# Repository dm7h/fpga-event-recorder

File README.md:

FPGA-Event-Recorder
-------------------

This project implements a FPGA based event recorder using the open source toolchain IceStorm. 
Similar to a logic analyzer it records logic level input signals, but in contrast to a logic analyzer it does not provide a continuous stream of the signal state. Instead the signals are filtered at capture time to match only relevant input combinations and signal changes. Using predefined events to filter the input stream is especially suitable for the analysis of known signals that are to be captured and examined at high temporal resolution.
The implementation of the event recorder is done on a Raspberry Pi Zero with a Lattice iCE40-based FPGA shield and is realized using the IcoSoc project with the IceStorm toolchain.   

### Getting started:

* install the IceStorm toolchain
see http://www.clifford.at/icestorm/#install

* install the RISC-V toolchain
```bash
git clone git@github.com:cliffordwolf/picorv32.git
cd picorv32
make download-tools
make -j$(nproc) build-tools                                                               
```
(can take a while)

* download the IcoSoc port for IceZero (on your local machine)
```bash
cd ..
git clone https://github.com/dm7h/icozsoc.git
```
* configure SSH on the raspi
```bash
# see: https://www.raspberrypi.org/documentation/remote-access/ssh/passwordless.md
# export ssh host, eg. pi@zero oder pi@192.168.1.43:
export SSH_RASPI=pi@zero
# check password-less ssh connection
ssh $SSH_RASPI                                                                               $
```
* install `icozctl` on the raspi 
```bash
git clone https://github.com/dm7h/icozctl
cd icozctl
sudo make install
```
* compile and flash the bitstream (local machine)
```bash
cd ../icosoc/examples/event-recorder/
make prog_flash
```
* on the raspi, edit `ìcozctl/config.yml` to your liking
```yaml
# event configuration
events: 
  - start:
          trigger: u
          funcion: start

  - stop:
          trigger: d
          function: stop

  - clk_up:
          trigger: 1u

  - clk_down:
          trigger: 1d
```
* start recording events `
```bash
icozctl -s -c config.yml -o midi_clock.vcd
```
see `icozctl -h` for options

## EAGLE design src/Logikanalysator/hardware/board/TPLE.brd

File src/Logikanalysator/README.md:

Logikanalysator
---------------

Hubert Högl, <Hubert.Hoegl@hs-augsburg.de>, 2017-12-04 

Das Logikanalysator-Projekt "USB-TPLE" entstand in der Bachelorarbeit
von Andreas Müller in 2010. Die Dateien aus der Bachelorarbeit sind im
Ordner 

```
USB-TPLE
```

Später wurde das Projekt in einer Projektarbeit im WS13/14 noch einmal
stark überarbeitet. Meine Aufgabenstellung ist auf dieser Wiki-Seite:

http://hhoegl.informatik.hs-augsburg.de/hhwiki/Logikanalysator

Die Ergebnisse sind in den Verzeichnissen:

```
cpld-firmware
Doku
Firmware-Mikrocontroller
hardware
jtag-LufaVirtualSerial
jtag-staplplayer
pc-software
signalgenerator-de1
sigrok-integration
```

In `Doku/Wiki/index.html` ist ein Grossteil der Doku aus dem Trac Wiki
übernommen:

  https://io.informatik.fh-augsburg.de/cgi-bin/trac_Logikanalysator.cgi/wiki/

Den damaligen "Trac" Projektserver gibt es immer noch:

* TRAC: https://io.informatik.fh-augsburg.de/trac/Logikanalysator
* SVN: https://io.informatik.fh-augsburg.de/svn/Logikanalysator
* DAV: https://io.informatik.fh-augsburg.de/dav/Logikanalysator (Software)
* WWW: https://io.informatik.fh-augsburg.de/projekte/Logikanalysator

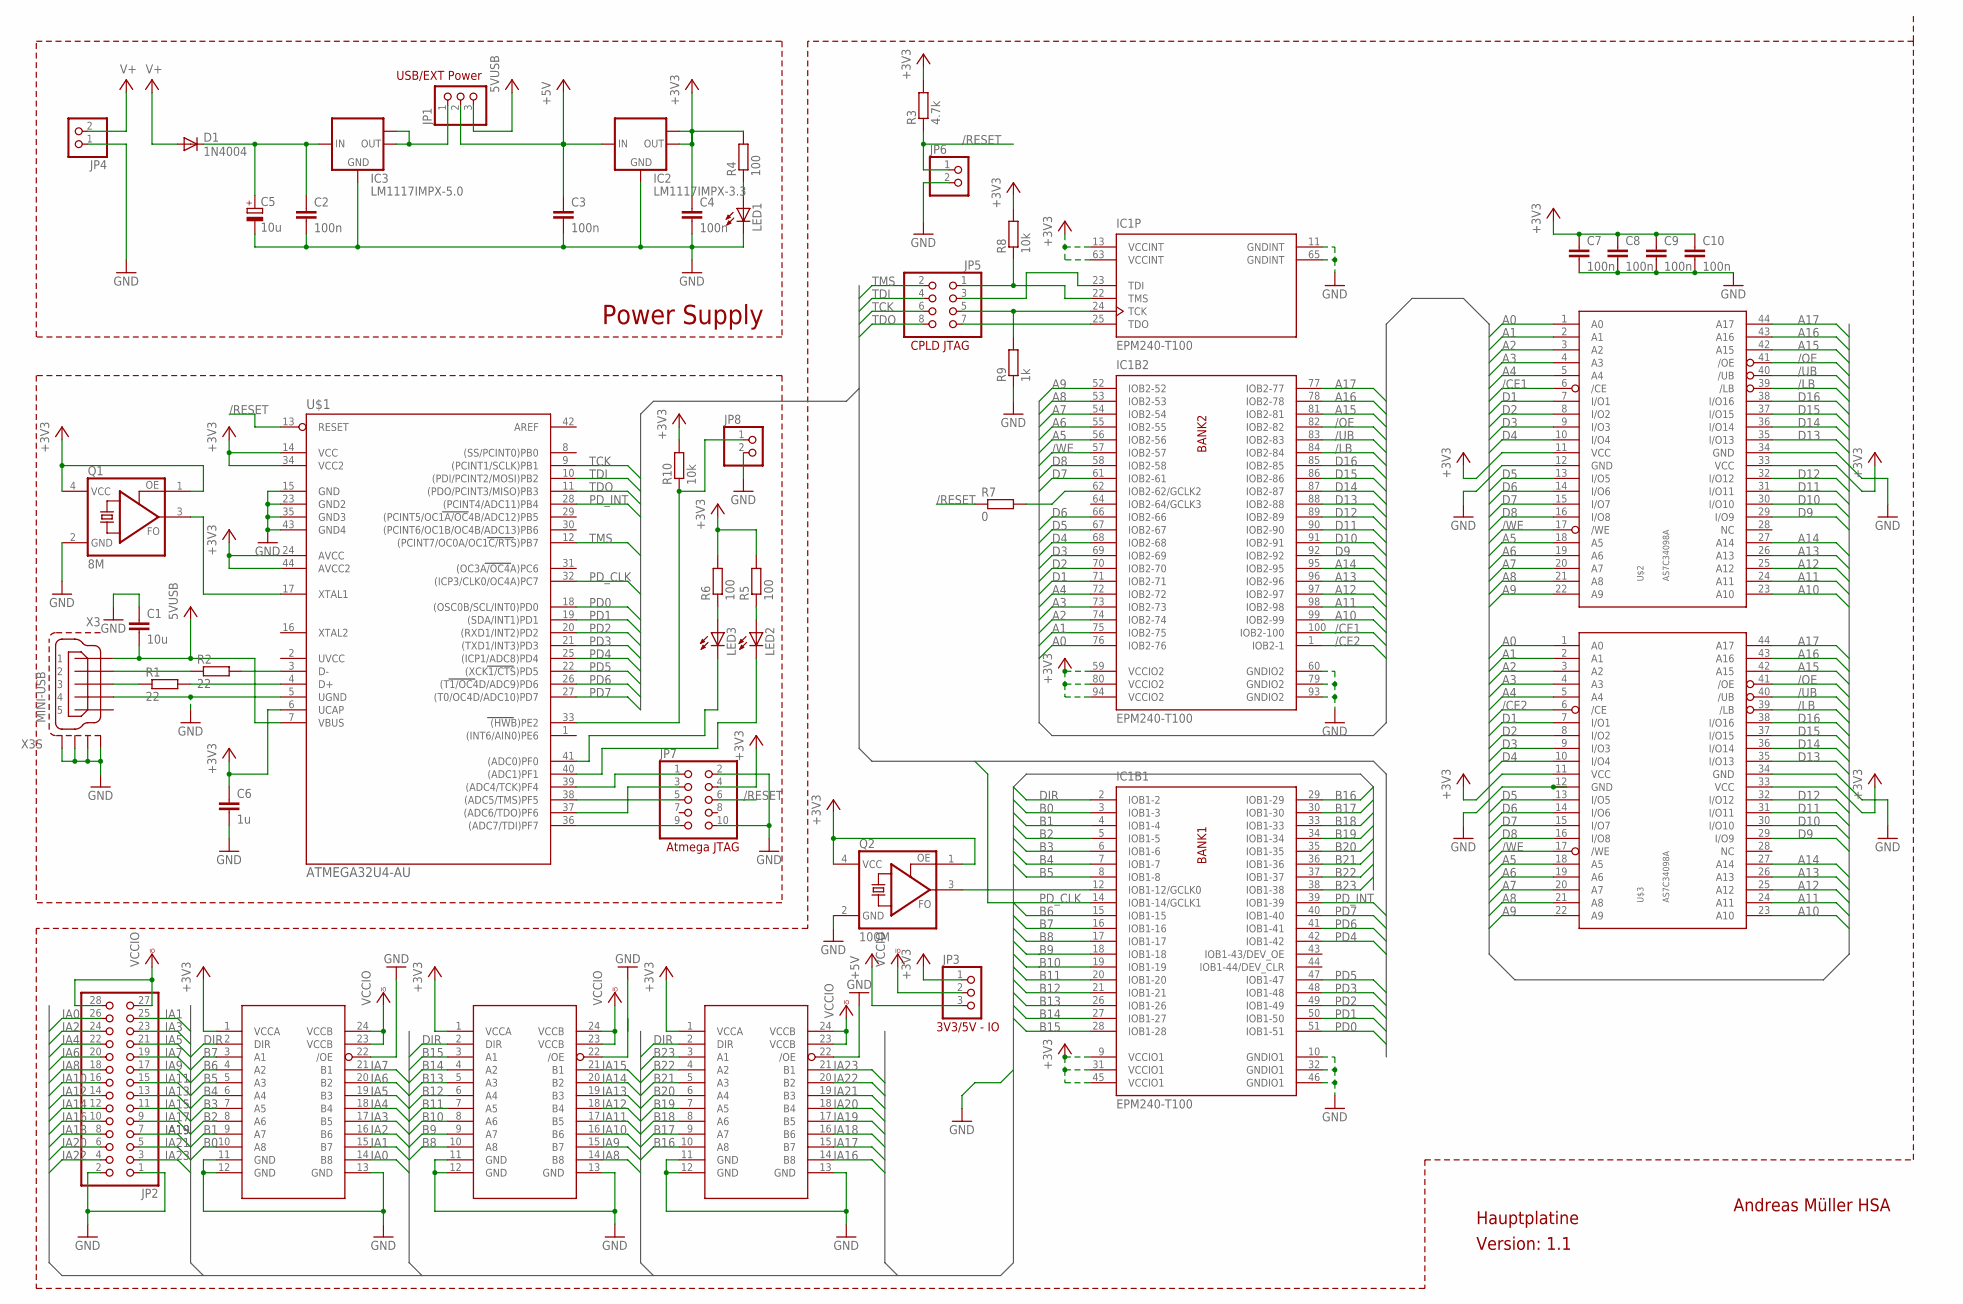
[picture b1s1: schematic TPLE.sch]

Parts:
C1: 10u; C3216
C2, C3, C4: 100n; C1206
C5: 10u; E2-5
C6: 1u; C0402
C7, C8, C9, C10: 100n; C0402
D1: 1N4004; DO41-10
IC1: EPM240-T100; TQFP100
IC2: LM1117IMPX-3.3; SOT223
IC3: LM1117IMPX-5.0; SOT223
JP1, JP3: PINHD-1X3; 1X03
JP2: PINHD-2X14; 2X14
JP4, JP6, JP8: PINHD-1X2; 1X02
JP5: PINHD-2X4; 2X04
JP7: PINHD-2X5; 2X05
LED1, LED2, LED3: LEDSMT1206; 1206
Q1: 8M; ASF
Q2: 100M; ASF
R1, R2: 22; M3216
R3: 4.7k; M3216
R4, R5, R6: 100; M3216
R7: 0; R0201
R8: 10k; M3216
R9: 1k; M3216
R10: 10k; R0402
U$1: ATMEGA32U4-AU; TQFP44
U$2, U$3: AS7C34098A; TSOP44-T2
U$4, U$5, U$6: SN74LVC8T245; TVSOP24
X3: MINI-USB; UX60A-MB-5ST

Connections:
+3V3: C4.1, C6.1, C7.1, C8.1, C9.1, C10.1, IC1.9 (VCCIO1), IC1.13 (VCCINT), IC1.31 (VCCIO1), IC1.45 (VCCIO1), IC1.59 (VCCIO2), IC1.63 (VCCINT), IC1.80 (VCCIO2), IC1.94 (VCCIO2), IC2.2 (OUT), IC2.TAB (OUT1), JP3.1, JP7.4, Q1.1 (OE), Q1.4 (VCC), Q2.1 (OE), Q2.4 (VCC), R3.2, R4.2, R5.2, R6.2, R8.2, R10.2, U$1.6 (UCAP), U$1.14 (VCC), U$1.24 (AVCC), U$1.34 (VCC2), U$1.44 (AVCC2), U$2.11 (VCC), U$2.33 (VCC), U$3.11 (VCC), U$3.33 (VCC), U$4.1 (VCCA), U$5.1 (VCCA), U$6.1 (VCCA)
+5V: C3.1, IC2.3 (IN), JP1.2, JP3.3
/CE1: IC1.100 (IOB2-100), U$2.6 (/CE)
/CE2: IC1.1 (IOB2-1), U$3.6 (/CE)
/LB: IC1.84 (IOB2-84), U$2.39 (/LB), U$3.39 (/LB)
/OE: IC1.82 (IOB2-82), U$2.41 (/OE), U$3.41 (/OE)
/RESET: JP6.1, JP7.6, R3.1, R7.1, U$1.13 (RESET)
/UB: IC1.83 (IOB2-83), U$2.40 (/UB), U$3.40 (/UB)
/WE: IC1.57 (IOB2-57), U$2.17 (/WE), U$3.17 (/WE)
A0: IC1.76 (IOB2-76), U$2.1 (A0), U$3.1 (A0)
A1: IC1.75 (IOB2-75), U$2.2 (A1), U$3.2 (A1)
A2: IC1.74 (IOB2-74), U$2.3 (A2), U$3.3 (A2)
A3: IC1.73 (IOB2-73), U$2.4 (A3), U$3.4 (A3)
A4: IC1.72 (IOB2-72), U$2.5 (A4), U$3.5 (A4)
A5: IC1.56 (IOB2-56), U$2.18 (A5), U$3.18 (A5)
A6: IC1.55 (IOB2-55), U$2.19 (A6), U$3.19 (A6)
A7: IC1.54 (IOB2-54), U$2.20 (A7), U$3.20 (A7)
A8: IC1.53 (IOB2-53), U$2.21 (A8), U$3.21 (A8)
A9: IC1.52 (IOB2-52), U$2.22 (A9), U$3.22 (A9)
A10: IC1.99 (IOB2-99), U$2.23 (A10), U$3.23 (A10)
A11: IC1.98 (IOB2-98), U$2.24 (A11), U$3.24 (A11)
A12: IC1.97 (IOB2-97), U$2.25 (A12), U$3.25 (A12)
A13: IC1.96 (IOB2-96), U$2.26 (A13), U$3.26 (A13)
A14: IC1.95 (IOB2-95), U$2.27 (A14), U$3.27 (A14)
A15: IC1.81 (IOB2-81), U$2.42 (A15), U$3.42 (A15)
A16: IC1.78 (IOB2-78), U$2.43 (A16), U$3.43 (A16)
A17: IC1.77 (IOB2-77), U$2.44 (A17), U$3.44 (A17)
B0: IC1.3 (IOB1-3), U$4.10 (A8)
B1: IC1.4 (IOB1-4), U$4.9 (A7)
B2: IC1.5 (IOB1-5), U$4.8 (A6)
B3: IC1.6 (IOB1-6), U$4.7 (A5)
B4: IC1.7 (IOB1-7), U$4.6 (A4)
B5: IC1.8 (IOB1-8), U$4.5 (A3)
B6: IC1.15 (IOB1-15), U$4.4 (A2)
B7: IC1.16 (IOB1-16), U$4.3 (A1)
B8: IC1.17 (IOB1-17), U$5.10 (A8)
B9: IC1.18 (IOB1-18), U$5.9 (A7)
B10: IC1.19 (IOB1-19), U$5.8 (A6)
B11: IC1.20 (IOB1-20), U$5.7 (A5)
B12: IC1.21 (IOB1-21), U$5.6 (A4)
B13: IC1.26 (IOB1-26), U$5.5 (A3)
B14: IC1.27 (IOB1-27), U$5.4 (A2)
B15: IC1.28 (IOB1-28), U$5.3 (A1)
B16: IC1.29 (IOB1-29), U$6.10 (A8)
B17: IC1.30 (IOB1-30), U$6.9 (A7)
B18: IC1.33 (IOB1-33), U$6.8 (A6)
B19: IC1.34 (IOB1-34), U$6.7 (A5)
B20: IC1.35 (IOB1-35), U$6.6 (A4)
B21: IC1.36 (IOB1-36), U$6.5 (A3)
B22: IC1.37 (IOB1-37), U$6.4 (A2)
B23: IC1.38 (IOB1-38), U$6.3 (A1)
D1: IC1.71 (IOB2-71), U$2.7 (I/O1), U$3.7 (I/O1)
D2: IC1.70 (IOB2-70), U$2.8 (I/O2), U$3.8 (I/O2)
D3: IC1.69 (IOB2-69), U$2.9 (I/O3), U$3.9 (I/O3)
D4: IC1.68 (IOB2-68), U$2.10 (I/O4), U$3.10 (I/O4)
D5: IC1.67 (IOB2-67), U$2.13 (I/O5), U$3.13 (I/O5)
D6: IC1.66 (IOB2-66), U$2.14 (I/O6), U$3.14 (I/O6)
D7: IC1.61 (IOB2-61), U$2.15 (I/O7), U$3.15 (I/O7)
D8: IC1.58 (IOB2-58), U$2.16 (I/O8), U$3.16 (I/O8)
D9: IC1.92 (IOB2-92), U$2.29 (I/O9), U$3.29 (I/O9)
D10: IC1.91 (IOB2-91), U$2.30 (I/O10), U$3.30 (I/O10)
D11: IC1.90 (IOB2-90), U$2.31 (I/O11), U$3.31 (I/O11)
D12: IC1.89 (IOB2-89), U$2.32 (I/O12), U$3.32 (I/O12)
D13: IC1.88 (IOB2-88), U$2.35 (I/O13), U$3.35 (I/O13)
D14: IC1.87 (IOB2-87), U$2.36 (I/O14), U$3.36 (I/O14)
D15: IC1.86 (IOB2-86), U$2.37 (I/O15), U$3.37 (I/O15)
D16: IC1.85 (IOB2-85), U$2.38 (I/O16), U$3.38 (I/O16)
DIR: IC1.2 (IOB1-2), U$4.2 (DIR), U$5.2 (DIR), U$6.2 (DIR)
GND: C1.1, C2.2, C3.2, C4.2, C5.-, C6.2, C7.2, C8.2, C9.2, C10.2, IC1.10 (GNDIO1), IC1.11 (GNDINT), IC1.32 (GNDIO1), IC1.46 (GNDIO1), IC1.60 (GNDIO2), IC1.65 (GNDINT), IC1.79 (GNDIO2), IC1.93 (GNDIO2), IC2.1 (GND), IC3.1 (GND), JP2.1, JP2.2, JP4.1, JP6.2, JP7.2, JP7.10, JP8.2, LED1.C, Q1.2 (GND), Q2.2 (GND), R9.1, U$1.5 (UGND), U$1.15 (GND), U$1.23 (GND2), U$1.35 (GND3), U$1.43 (GND4), U$2.12 (GND), U$2.34 (GND), U$3.12 (GND), U$3.34 (GND), U$4.11 (GND), U$4.12 (GND), U$4.13 (GND), U$4.22 (/OE), U$5.11 (GND), U$5.12 (GND), U$5.13 (GND), U$5.22 (/OE), U$6.11 (GND), U$6.12 (GND), U$6.13 (GND), U$6.22 (/OE), X3.4, X3.M1 (S1), X3.M2 (S2), X3.M3 (S3), X3.M4 (S4)
IA0: JP2.26, U$4.14 (B8)
IA1: JP2.25, U$4.15 (B7)
IA2: JP2.24, U$4.16 (B6)
IA3: JP2.23, U$4.17 (B5)
IA4: JP2.22, U$4.18 (B4)
IA5: JP2.21, U$4.19 (B3)
IA6: JP2.20, U$4.20 (B2)
IA7: JP2.19, U$4.21 (B1)
IA8: JP2.18, U$5.14 (B8)
IA9: JP2.17, U$5.15 (B7)
IA10: JP2.16, U$5.16 (B6)
IA11: JP2.15, U$5.17 (B5)
IA12: JP2.14, U$5.18 (B4)
IA13: JP2.13, U$5.19 (B3)
IA14: JP2.12, U$5.20 (B2)
IA15: JP2.11, U$5.21 (B1)
IA16: JP2.10, U$6.14 (B8)
IA17: JP2.9, U$6.15 (B7)
IA18: JP2.8, U$6.16 (B6)
IA19: JP2.7, U$6.17 (B5)
IA20: JP2.6, U$6.18 (B4)
IA21: JP2.5, U$6.19 (B3)
IA22: JP2.4, U$6.20 (B2)
IA23: JP2.3, U$6.21 (B1)
unnamed: R2.1, X3.2
unnamed: R2.2, U$1.3 (D-)
unnamed: R1.1, X3.3
unnamed: R1.2, U$1.4 (D+)
unnamed: IC3.2 (OUT), IC3.TAB (OUT1), JP1.1
unnamed: IC1.23 (TDI), JP5.3
unnamed: C2.1, C5.+, D1.C, IC3.3 (IN)
unnamed: IC1.22 (TMS), JP5.1, R8.1
unnamed: IC1.24 (TCK), JP5.5, R9.2
unnamed: IC1.25 (TDO), JP5.7
unnamed: JP7.1, U$1.39 ((ADC4/TCK)PF4)
unnamed: JP7.3, U$1.37 ((ADC6/TDO)PF6)
unnamed: JP7.5, U$1.38 ((ADC5/TMS)PF5)
unnamed: JP7.9, U$1.36 ((ADC7/TDI)PF7)
unnamed: IC1.62 (IOB2-62/GCLK2), R7.2
unnamed: JP8.1, R10.1, U$1.33 ((HWB)PE2)
unnamed: Q1.3 (FO), U$1.17 (XTAL1)
unnamed: IC1.12 (IOB1-12/GCLK0), Q2.3 (FO)
unnamed: LED1.A, R4.1
unnamed: LED2.C, U$1.40 ((ADC1)PF1)
unnamed: LED3.C, U$1.41 ((ADC0)PF0)
unnamed: LED2.A, R5.1
unnamed: LED3.A, R6.1
PD0: IC1.51 (IOB1-51), U$1.18 ((OSC0B/SCL/INT0)PD0)
PD1: IC1.50 (IOB1-50), U$1.19 ((SDA/INT1)PD1)
PD2: IC1.49 (IOB1-49), U$1.20 ((RXD1/INT2)PD2)
PD3: IC1.48 (IOB1-48), U$1.21 ((TXD1/INT3)PD3)
PD4: IC1.42 (IOB1-42), U$1.25 ((ICP1/ADC8)PD4)
PD5: IC1.47 (IOB1-47), U$1.22 ((XCK1/CTS)PD5)
PD6: IC1.41 (IOB1-41), U$1.26 ((T1/OC4D/ADC9)PD6)
PD7: IC1.40 (IOB1-40), U$1.27 ((T0/OC4D/ADC10)PD7)
PD_CLK: IC1.14 (IOB1-14/GCLK1), U$1.32 ((ICP3/CLK0/OC4A)PC7)
PD_INT: IC1.39 (IOB1-39), U$1.28 ((PCINT4/ADC11)PB4)
TCK: JP5.6, U$1.9 ((PCINT1/SCLK)PB1)
TDI: JP5.4, U$1.10 ((PDI/PCINT2/MOSI)PB2)
TDO: JP5.8, U$1.11 ((PDO/PCINT3/MISO)PB3)
TMS: JP5.2, U$1.12 ((PCINT7/OC0A/OC1C/RTS)PB7)
V+: D1.A, JP4.2
VCC: C1.2, JP1.3, U$1.7 (VBUS), X3.1
VCCIO: JP2.27, JP2.28, JP3.2, U$4.23 (VCCB), U$4.24 (VCCB), U$5.23 (VCCB), U$5.24 (VCCB), U$6.23 (VCCB), U$6.24 (VCCB)

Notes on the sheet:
Power Supply
USB/EXT Power
Atmega JTAG
CPLD JTAG
3V3/5V - IO
Version: 1.1
Hauptplatine
Andreas Müller HSA

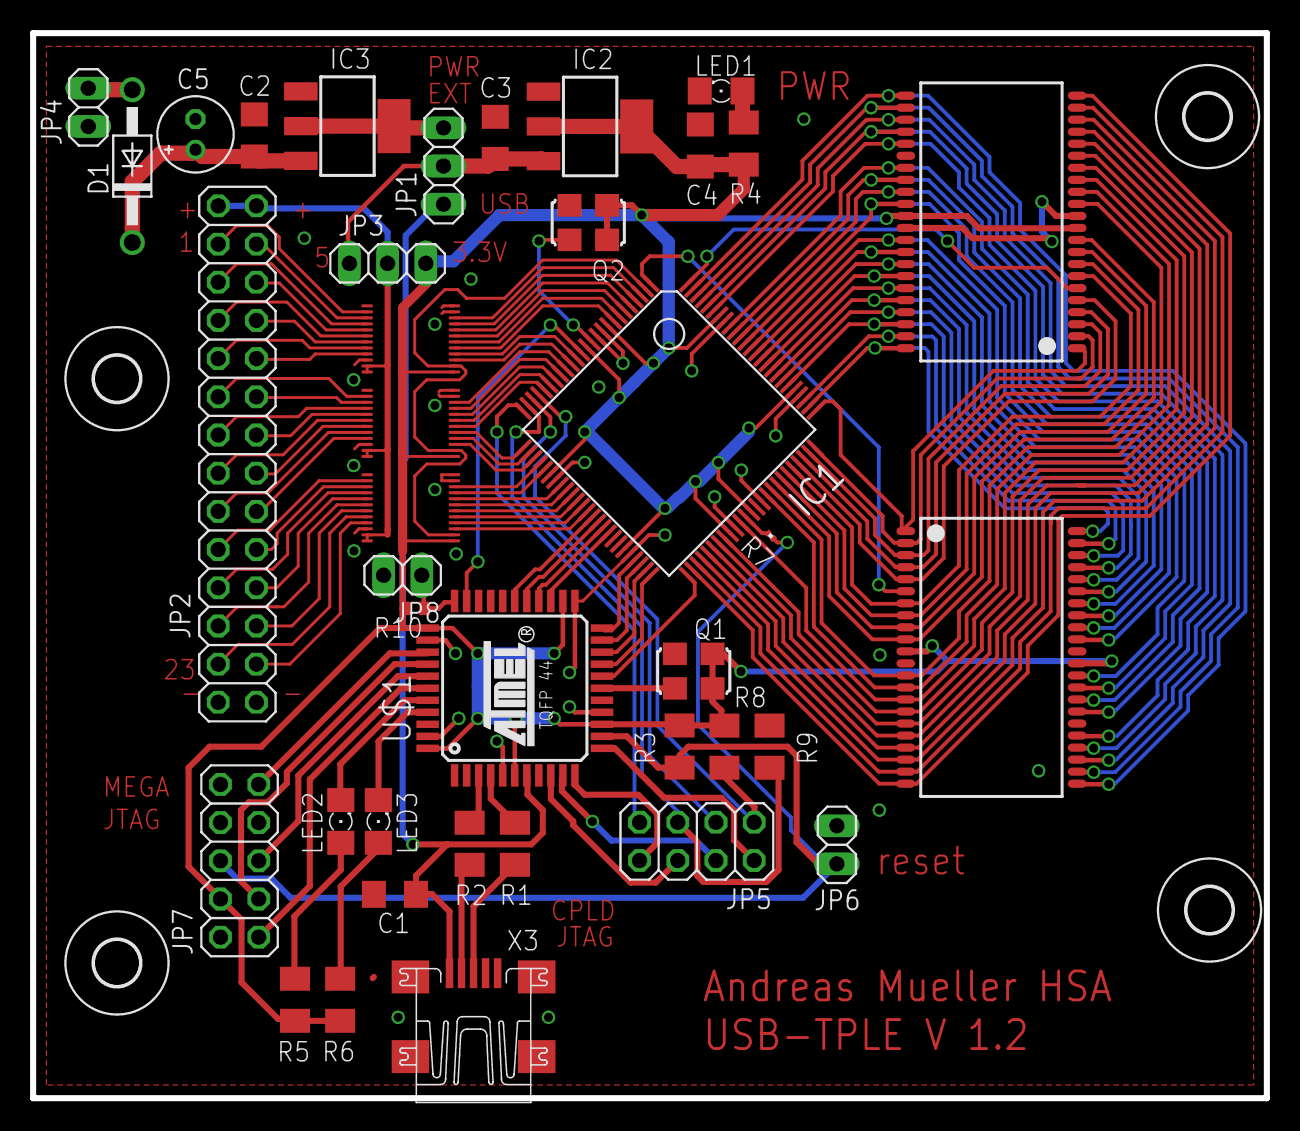
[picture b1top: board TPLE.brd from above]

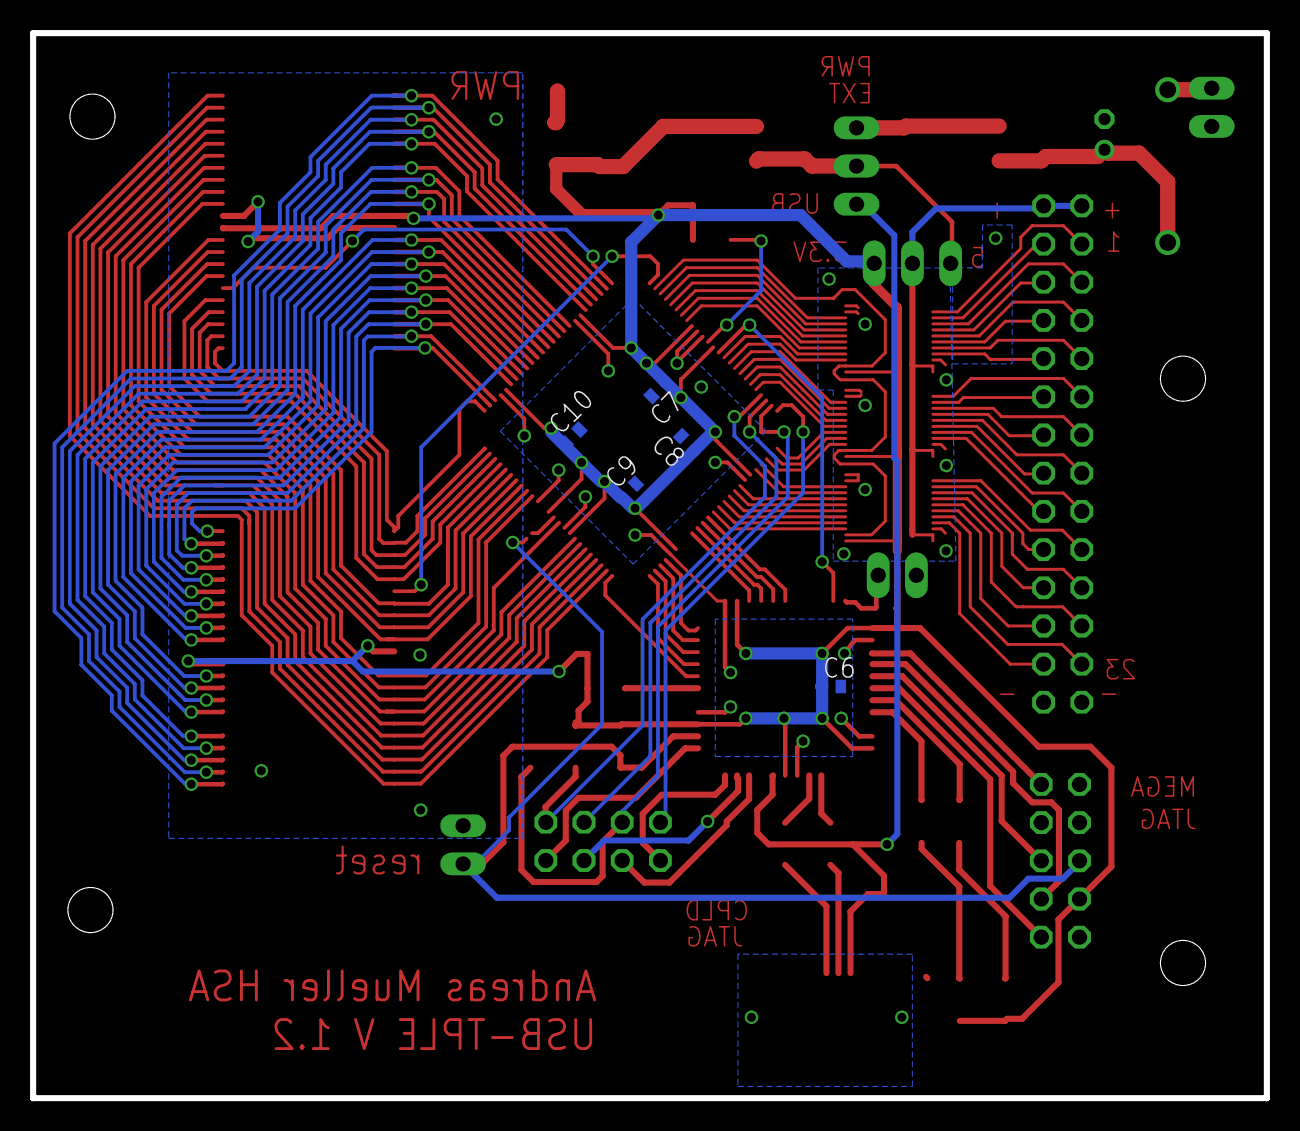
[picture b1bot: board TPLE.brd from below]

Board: 2 copper layers, 82.1 x 70.8 mm, 48 parts (5 on the bottom side), 133 nets.

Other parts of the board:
U$7, U$8, U$9, U$10: 3,0

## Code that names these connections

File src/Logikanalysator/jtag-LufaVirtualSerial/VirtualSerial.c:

/*
             LUFA Library
     Copyright (C) Dean Camera, 2013.

  dean [at] fourwalledcubicle [dot] com
           www.lufa-lib.org
*/

/*
  Copyright 2013  Dean Camera (dean [at] fourwalledcubicle [dot] com)

  Permission to use, copy, modify, distribute, and sell this
  software and its documentation for any purpose is hereby granted
  without fee, provided that the above copyright notice appear in
  all copies and that both that the copyright notice and this
  permission notice and warranty disclaimer appear in supporting
  documentation, and that the name of the author not be used in
  advertising or publicity pertaining to distribution of the
  software without specific, written prior permission.

  The author disclaims all warranties with regard to this
  software, including all implied warranties of merchantability
  and fitness.  In no event shall the author be liable for any
  special, indirect or consequential damages or any damages
  whatsoever resulting from loss of use, data or profits, whether
  in an action of contract, negligence or other tortious action,
  arising out of or in connection with the use or performance of
  this software.
*/

/** \file
 *
 *  Main source file for the VirtualSerial demo. This file contains the main tasks of
 *  the demo and is responsible for the initial application hardware configuration.
 */

#include "VirtualSerial.h"

#define JTAG_PORT       PORTB
#define JTAG_DDR        DDRB
#define JTAG_PIN        PINB
#define JTAG_TCK        PB1
#define JTAG_TDI        PB2
#define JTAG_TDO        PB3
#define JTAG_TDO_RDIND  PB4 /* TDO read indication */
#define JTAG_TMS        PB7

/** LUFA CDC Class driver interface configuration and state information. This structure is
 *  passed to all CDC Class driver functions, so that multiple instances of the same class
 *  within a device can be differentiated from one another.
 */
USB_ClassInfo_CDC_Device_t VirtualSerial_CDC_Interface =
	{
		.Config =
			{
				.ControlInterfaceNumber   = 0,
				.DataINEndpoint           =
					{
						.Address          = CDC_TX_EPADDR,
						.Size             = CDC_TXRX_EPSIZE,
						.Banks            = 1,
					},
				.DataOUTEndpoint =
					{
						.Address          = CDC_RX_EPADDR,
						.Size             = CDC_TXRX_EPSIZE,
						.Banks            = 1,
					},
				.NotificationEndpoint =
					{
						.Address          = CDC_NOTIFICATION_EPADDR,
						.Size             = CDC_NOTIFICATION_EPSIZE,
						.Banks            = 1,
					},
			},
	};

/** Standard file stream for the CDC interface when set up, so that the virtual CDC COM port can be
 *  used like any regular character stream in the C APIs
 */
static FILE USBSerialStream;


/** Main program entry point. This routine contains the overall program flow, including initial
 *  setup of all components and the main program loop.
 */
int main(void)
{
        int16_t c_in;
	uint8_t c_out;

	SetupHardware();

	/* Create a regular character stream for the interface so that it can be used with the stdio.h functions */
	CDC_Device_CreateStream(&VirtualSerial_CDC_Interface, &USBSerialStream);

	//LEDs_SetAllLEDs(LEDMASK_USB_NOTREADY);
	GlobalInterruptEnable();

	for (;;)
	{
		/* Must throw away unused bytes from the host, or it will lock up while waiting for the device */
		c_in = CDC_Device_ReceiveByte(&VirtualSerial_CDC_Interface);
                if(c_in > 0)
                {
			// write TCK, TDI, TMS
			JTAG_PORT = (uint8_t)c_in;

			// read TDO
			c_out = JTAG_PIN | (uint8_t)0x01; // will serial interface send if JTAG_PIN == 0x00?
			
                	CDC_Device_SendByte(&VirtualSerial_CDC_Interface, c_out );
		}

		CDC_Device_USBTask(&VirtualSerial_CDC_Interface);
		USB_USBTask();
	}
}

/*static inline void Serial_Disable(void)
{
	UCSR1B = 0;
	UCSR1A = 0;
	UCSR1C = 0;

	UBRR1  = 0;

	DDRD  &= ~(1 << 3);
	PORTD &= ~(1 << 2);
}*/

/** Configures the board hardware and chip peripherals for the demo's functionality. */
void SetupHardware(void)
{
#if (ARCH == ARCH_AVR8)
	/* Disable watchdog if enabled by bootloader/fuses */
	MCUSR &= ~(1 << WDRF);
	wdt_disable();

	/* Disable clock division */
	clock_prescale_set(clock_div_1);
#elif (ARCH == ARCH_XMEGA)
	/* Start the PLL to multiply the 2MHz RC oscillator to 32MHz and switch the CPU core to run from it */
	XMEGACLK_StartPLL(CLOCK_SRC_INT_RC2MHZ, 2000000, F_CPU);
	XMEGACLK_SetCPUClockSource(CLOCK_SRC_PLL);

	/* Start the 32MHz internal RC oscillator and start the DFLL to increase it to 48MHz using the USB SOF as a reference */
	XMEGACLK_StartInternalOscillator(CLOCK_SRC_INT_RC32MHZ);
	XMEGACLK_StartDFLL(CLOCK_SRC_INT_RC32MHZ, DFLL_REF_INT_USBSOF, F_USB);

	PMIC.CTRL = PMIC_LOLVLEN_bm | PMIC_MEDLVLEN_bm | PMIC_HILVLEN_bm;
#endif

	/* Hardware Initialization */
	//LEDs_Init();
	USB_Init();
	//Serial_Disable();


	// Set Data Direction Register for JTAG Port
	JTAG_DDR |=  ( (1 << JTAG_TCK) | (1 << JTAG_TDI) | (1 << JTAG_TMS) | (1 << JTAG_TDO_RDIND) ); // outputs
	JTAG_DDR &= ~(1 << JTAG_TDO); // inputs

	// Initialize Port with zeros (all outputs low/ off)
	JTAG_PORT = 0x00;
}


/** Event handler for the library USB Connection event. */
void EVENT_USB_Device_Connect(void)
{
	//LEDs_SetAllLEDs(LEDMASK_USB_ENUMERATING);
}

/** Event handler for the library USB Disconnection event. */
void EVENT_USB_Device_Disconnect(void)
{
	//LEDs_SetAllLEDs(LEDMASK_USB_NOTREADY);
}

/** Event handler for the library USB Configuration Changed event. */
void EVENT_USB_Device_ConfigurationChanged(void)
{
	bool ConfigSuccess = true;

	ConfigSuccess &= CDC_Device_ConfigureEndpoints(&VirtualSerial_CDC_Interface);

	//LEDs_SetAllLEDs(ConfigSuccess ? LEDMASK_USB_READY : LEDMASK_USB_ERROR);
}

/** Event handler for the library USB Control Request reception event. */
void EVENT_USB_Device_ControlRequest(void)
{
	CDC_Device_ProcessControlRequest(&VirtualSerial_CDC_Interface);
}

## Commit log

2018-02-23 init README
2018-02-23 initial code push
2018-02-23 dir structure
2018-02-23 clean code
2018-02-23 init code
2018-02-23 initial code update
2018-02-23 Add license
2018-02-23 initial push pi zero files and code
2018-02-23 add latex template for theses
2018-03-10 init ev test icosoc project
2018-03-10 add icezprog to Makefile for flashing the soc .bin file
2018-03-10 fix Makefile generation with icezprog
2018-03-29 raspif & SPI tests
2018-04-11 spi & raspi_if tests ..
2018-04-11 spi & raspi_if tests ...
2018-04-12 fix "make pdf"
2018-05-03 make icoprog work with icezero (flash mode)
2018-05-03 restore icezprog.c
2018-05-09 dhcpd settings for pi zero
2018-05-09 dhcpd readme
2018-05-12 spi flash debugging changes and picosoc port
2018-05-12 icoprog merge
2018-05-12 add icozctl and change Makefile to use it
2018-05-12 Makefile fix
2018-05-12 yaml config file + config parsing + trigger encoding
2018-05-17 uart config
2018-05-17 more cleverer trigger encoding
2018-05-17 remove raspif, uart and add spi
2018-05-21 spi slave module and debugging
2018-05-21 spi slave changes
2018-05-24 icozctl changes
2018-05-24 trigger configuration/logic and fifo testing
2018-05-26 adjust template, add glossary etc.
2018-06-01 thesis: einführung
2018-06-01 triggerrec fifo etc
2018-06-01 raspi update
2018-06-04 verilog trigger/event detection etc.
2018-06-04 save as .vcd etc.
2018-06-14 changes to C- and verilog event detection + thesis
2018-06-15 cleanup misc code
2018-06-15 various tests
2018-06-15 del LICENSE
2018-06-15 add ISC LICENSE
2018-06-15 fix icozprog (sram mode) & Makefile
2018-06-15 cleanup icozero subfolder
2018-06-18 thesis: implementation
2018-06-18 thesis: implementation II
2018-06-19 final pre-deadline update (pi)
2018-06-19 final pre-deadline update
2018-06-19 another final pre-deadline update
2018-06-19 yet another final pre-deadline update
